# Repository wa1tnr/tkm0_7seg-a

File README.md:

# tkm0_7seg-a
Sat Apr 27 22:03:36 UTC 2019

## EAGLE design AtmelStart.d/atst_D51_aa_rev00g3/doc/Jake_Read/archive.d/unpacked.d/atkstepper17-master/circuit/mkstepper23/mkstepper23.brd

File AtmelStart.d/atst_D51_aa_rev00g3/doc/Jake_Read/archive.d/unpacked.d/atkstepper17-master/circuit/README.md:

# AutomataKit Stepper17 Circuit Design

The circuit uses an ATXmega256A3U microcontroller and a TMC2130 step driver to do the business. Between the two are an SPI bus, to configure the driver, two diagnosis lines, a step, direction, and enable lines.

The TMC2130 is a popular step driver, and can sink ~ 1.5A of current. 

Power is bussed into the board with two M3 Screw Terminals. The board is not polarity protected. Data is delivered on an Automatakit Port, which includes a data line (uart TX / RX) and clock lines (CLKIN and CLKOUT)

## Next Circuit

 - on current scaling, get rid of PWM circuit and line out, use internal ref, and choose resistors with math: want 0.5 - 1.2A to be inside of 16-32 selection
 - go to 2oz copper bc u fancy, etc	
 - get rid of this split gnd

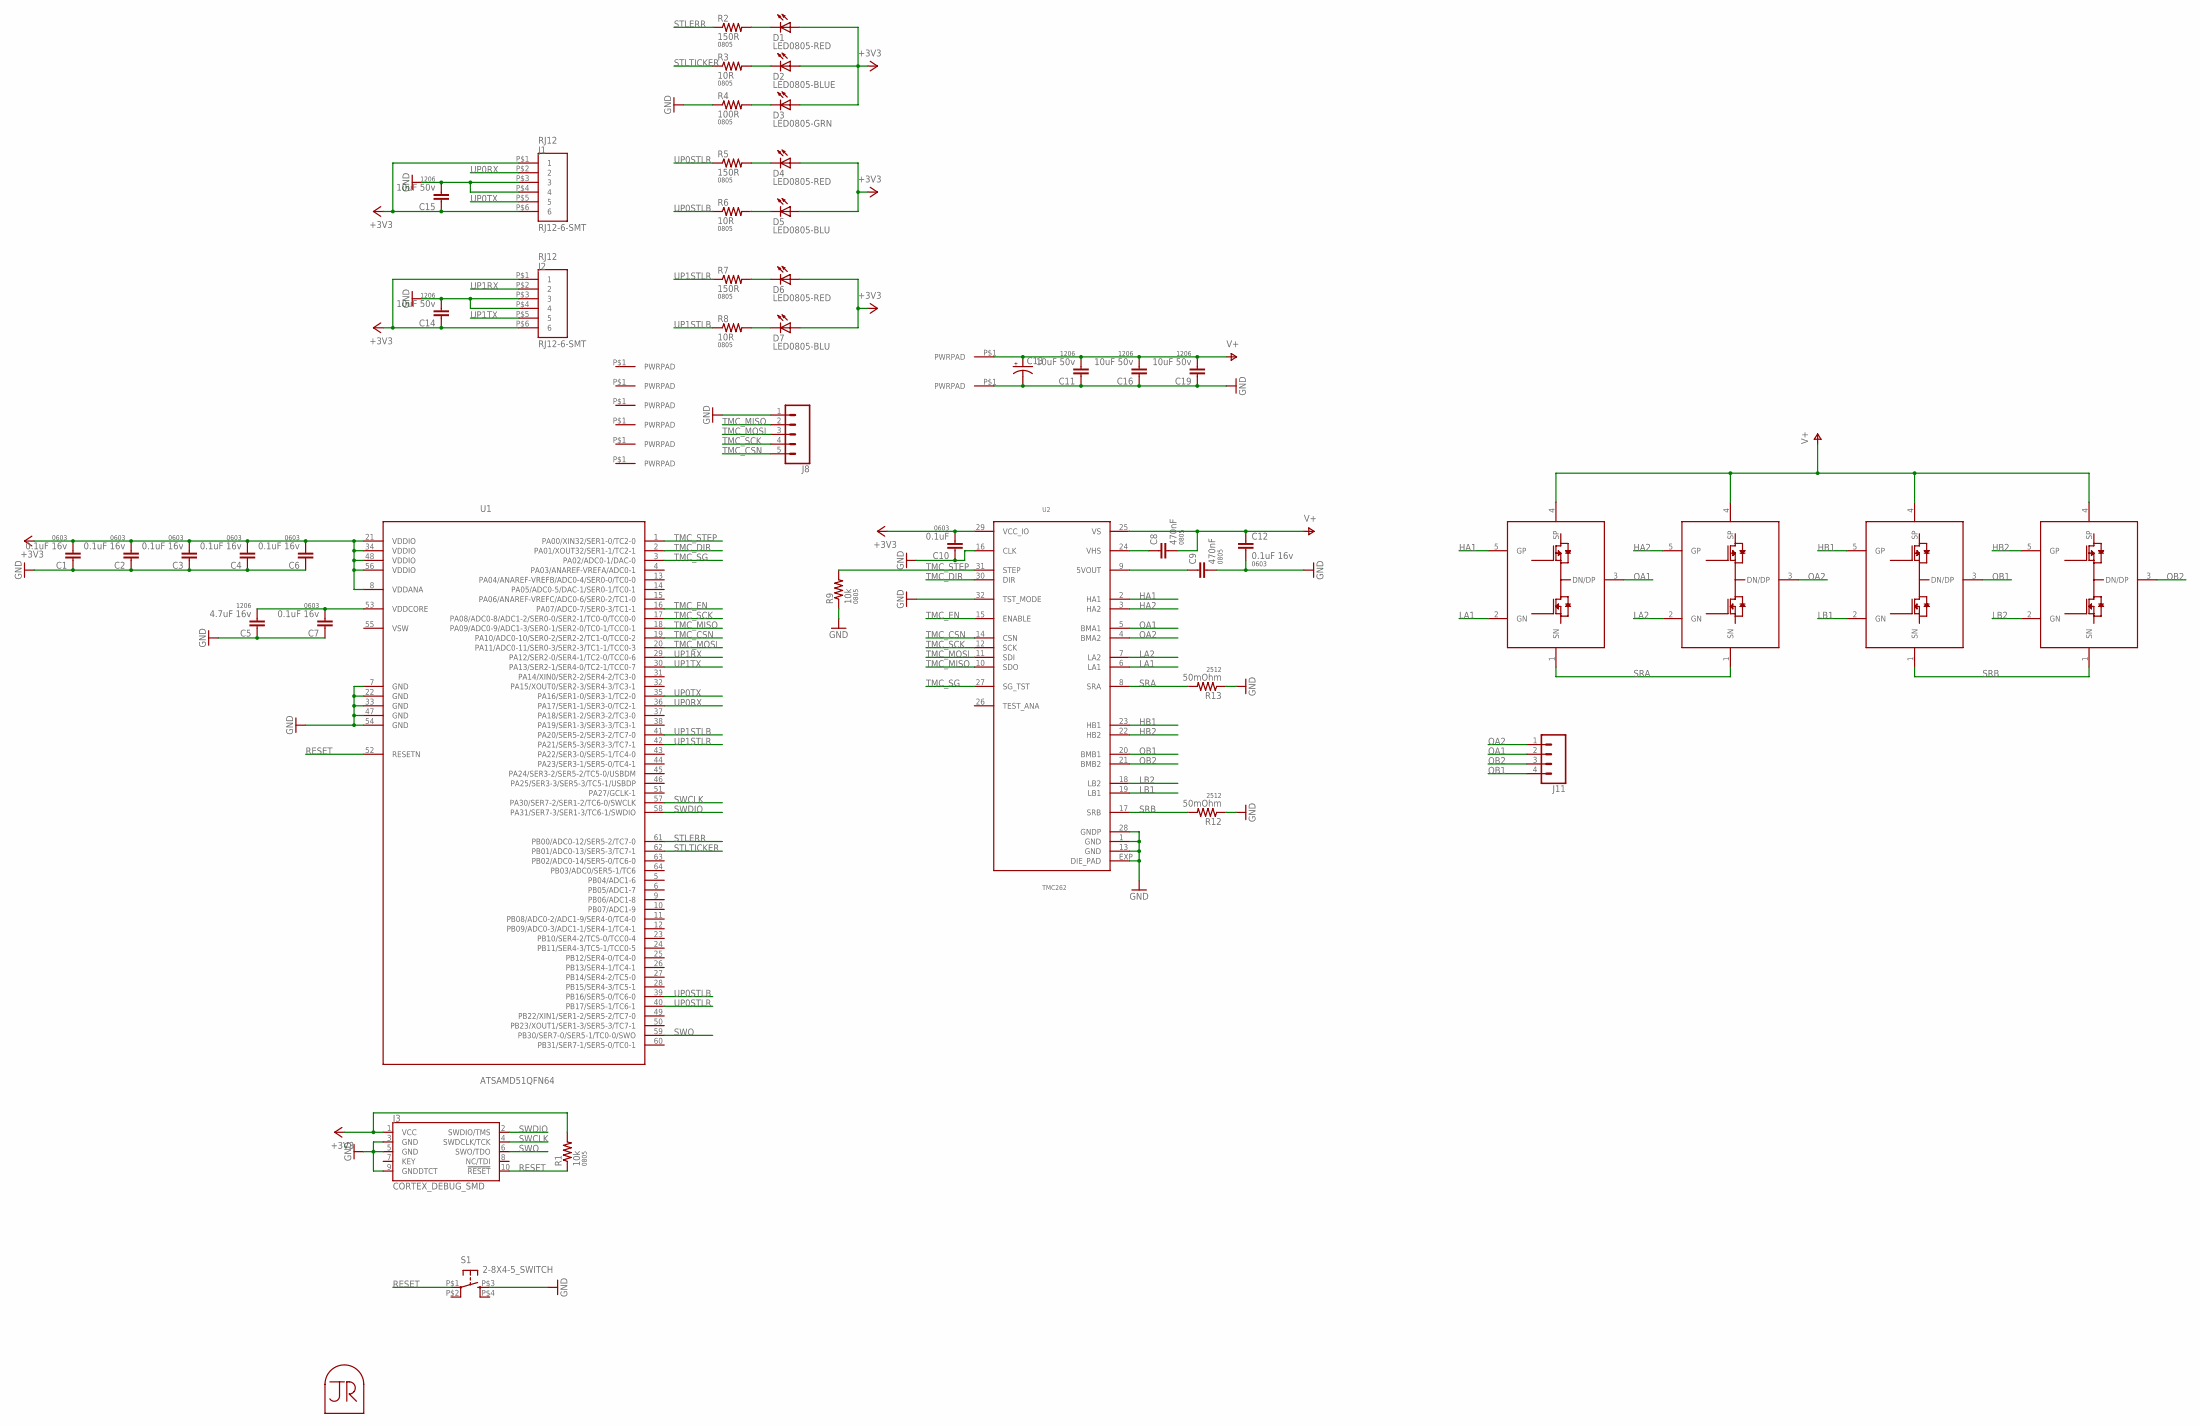
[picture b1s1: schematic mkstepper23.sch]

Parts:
C1, C2, C3, C4, C6, C7, C12: 0.1uF 16v; 0603-CAP
C5: 4.7uF 16v; 1206
C8, C9: 470nF; 0805
C10: 0.1uF; 0603-CAP
C11, C14, C15, C16, C19: 10uF 50v; 1206
C13: CAP-POL-6.6X6.6; 6.6X6.6-CAP
D1, D4, D6: LED0805-RED; LED0805
D2: LED0805-BLUE; LED0805
D3: LED0805-GRN; LED0805
D5, D7: LED0805-BLU; LED0805
J1, J2: RJ12-6-SMT
J3: CORTEX_DEBUG_SMD; SAMTECH_FTSH-105-01
J4, J5, J6, J7, J12, J13: PWRPADM3-SKINNY; PWRPAD_3-25MM-SKINNY
J8: CONN_05NO_SILK; 1X05_NO_SILK
J9, J10: PWRPAD; PWRPAD_M3-PEM-MOUNT
J11: CONN_04LONGPADS; 1X04_LONGPADS
MP1: JRTOMBSTONE
Q1, Q2, Q3, Q4: PNPAIR-FDD8424H; DPAK-5
R1, R9: 10k; 0805
R2, R5, R7: 150R; 0805
R3, R6, R8: 10R; 0805
R4: 100R; 0805
R12, R13: 50mOhm; R2512
S1: 2-8X4-5_SWITCH; TACT-SWITCH-KMR6
U1: ATSAMD51QFN64; QFN-64-9X9MM
U2: TMC262; QFN32

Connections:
+3V3: C1.2, C2.2, C3.2, C4.2, C6.2, C10.2, C14.1, C15.1, D1.1 (A), D2.1 (A), D3.1 (A), D4.1 (A), D5.1 (A), D6.1 (A), D7.1 (A), J1.P$1 (1), J1.P$6 (6), J2.P$1 (1), J2.P$6 (6), J3.1 (VCC), R1.2, U1.8 (VDDANA), U1.21 (VDDIO), U1.34 (VDDIO), U1.48 (VDDIO), U1.56 (VDDIO), U2.29 (VCC_IO)
GND: C1.1, C2.1, C3.1, C4.1, C5.1, C6.1, C7.1, C9.2, C10.1, C11.1, C12.2, C13.-, C14.2, C15.2, C16.1, C19.1, J1.P$3 (3), J1.P$4 (4), J2.P$3 (3), J2.P$4 (4), J3.3 (GND), J3.5 (GND), J3.9 (GNDDTCT), J8.1, J10.P$1, R4.1, R9.1, R12.1, R13.1, S1.P$3 (S), U1.7 (GND), U1.22 (GND), U1.33 (GND), U1.47 (GND), U1.54 (GND), U2.1 (GND), U2.13 (GND), U2.16 (CLK), U2.28 (GNDP), U2.32 (TST_MODE), U2.EXP (DIE_PAD)
HA1: Q1.5 (GP), U2.2 (HA1)
HA2: Q2.5 (GP), U2.3 (HA2)
HB1: Q3.5 (GP), U2.23 (HB1)
HB2: Q4.5 (GP), U2.22 (HB2)
LA1: Q1.2 (GN), U2.6 (LA1)
LA2: Q2.2 (GN), U2.7 (LA2)
LB1: Q3.2 (GN), U2.19 (LB1)
LB2: Q4.2 (GN), U2.18 (LB2)
unnamed: D3.2 (C), R4.2
unnamed: C8.1, U2.24 (VHS)
unnamed: C9.1, U2.9 (5VOUT)
unnamed: D2.2 (C), R3.2
unnamed: D1.2 (C), R2.2
unnamed: C5.2, C7.2, U1.53 (VDDCORE)
unnamed: D4.2 (C), R5.2
unnamed: D5.2 (C), R6.2
unnamed: D6.2 (C), R7.2
unnamed: D7.2 (C), R8.2
OA1: J11.2, Q1.3 (DN/DP), U2.5 (BMA1)
OA2: J11.1, Q2.3 (DN/DP), U2.4 (BMA2)
OB1: J11.4, Q3.3 (DN/DP), U2.20 (BMB1)
OB2: J11.3, Q4.3 (DN/DP), U2.21 (BMB2)
RESET: J3.10 (!RESET), R1.1, S1.P$1, U1.52 (RESETN)
SRA: Q1.1 (SN), Q2.1 (SN), R13.2, U2.8 (SRA)
SRB: Q3.1 (SN), Q4.1 (SN), R12.2, U2.17 (SRB)
STLERR: R2.1, U1.61 (PB00/ADC0-12/SER5-2/TC7-0)
STLTICKER: R3.1, U1.62 (PB01/ADC0-13/SER5-3/TC7-1)
SWCLK: J3.4 (SWDCLK/TCK), U1.57 (PA30/SER7-2/SER1-2/TC6-0/SWCLK)
SWDIO: J3.2 (SWDIO/TMS), U1.58 (PA31/SER7-3/SER1-3/TC6-1/SWDIO)
SWO: J3.6 (SWO/TDO), U1.59 (PB30/SER7-0/SER5-1/TC0-0/SWO)
TMC_CSN: J8.5, U1.19 (PA10/ADC0-10/SER0-2/SER2-2/TC1-0/TCC0-2), U2.14 (CSN)
TMC_DIR: U1.2 (PA01/XOUT32/SER1-1/TC2-1), U2.30 (DIR)
TMC_EN: U1.16 (PA07/ADC0-7/SER0-3/TC1-1), U2.15 (ENABLE)
TMC_MISO: J8.2, U1.18 (PA09/ADC0-9/ADC1-3/SER0-1/SER2-0/TC0-1/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), U2.10 (SDO)
TMC_MOSI: J8.3, U1.20 (PA11/ADC0-11/SER0-3/SER2-3/TC1-1/TCC0-3), U2.11 (SDI)
TMC_SCK: J8.4, U1.17 (PA08/ADC0-8/ADC1-2/SER0-0/SER2-1/TC0-0/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), U2.12 (SCK)
TMC_SG: U1.3 (PA02/ADC0-1/DAC-0), U2.27 (SG_TST)
TMC_STEP: R9.2, U1.1 (PA00/XIN32/SER1-0/TC2-0), U2.31 (STEP)
UP0RX: J1.P$2 (2), U1.36 (PA17/SER1-1/SER3-0/TC2-1)
UP0STLB: R6.1, U1.39 (PB16/SER5-0/TC6-0)
UP0STLR: R5.1, U1.40 (PB17/SER5-1/TC6-1)
UP0TX: J1.P$5 (5), U1.35 (PA16/SER1-0/SER3-1/TC2-0)
UP1RX: J2.P$2 (2), U1.29 (PA12/SER2-0/SER4-1/TC2-0/TCC0-6)
UP1STLB: R8.1, U1.41 (PA20/SER5-2/SER3-2/TC7-0)
UP1STLR: R7.1, U1.42 (PA21/SER5-3/SER3-3/TC7-1)
UP1TX: J2.P$5 (5), U1.30 (PA13/SER2-1/SER4-0/TC2-1/TCC0-7)
V+: C8.2, C11.2, C12.1, C13.+, C16.2, C19.2, J9.P$1, Q1.4 (SP), Q2.4 (SP), Q3.4 (SP), Q4.4 (SP), U2.25 (VS)

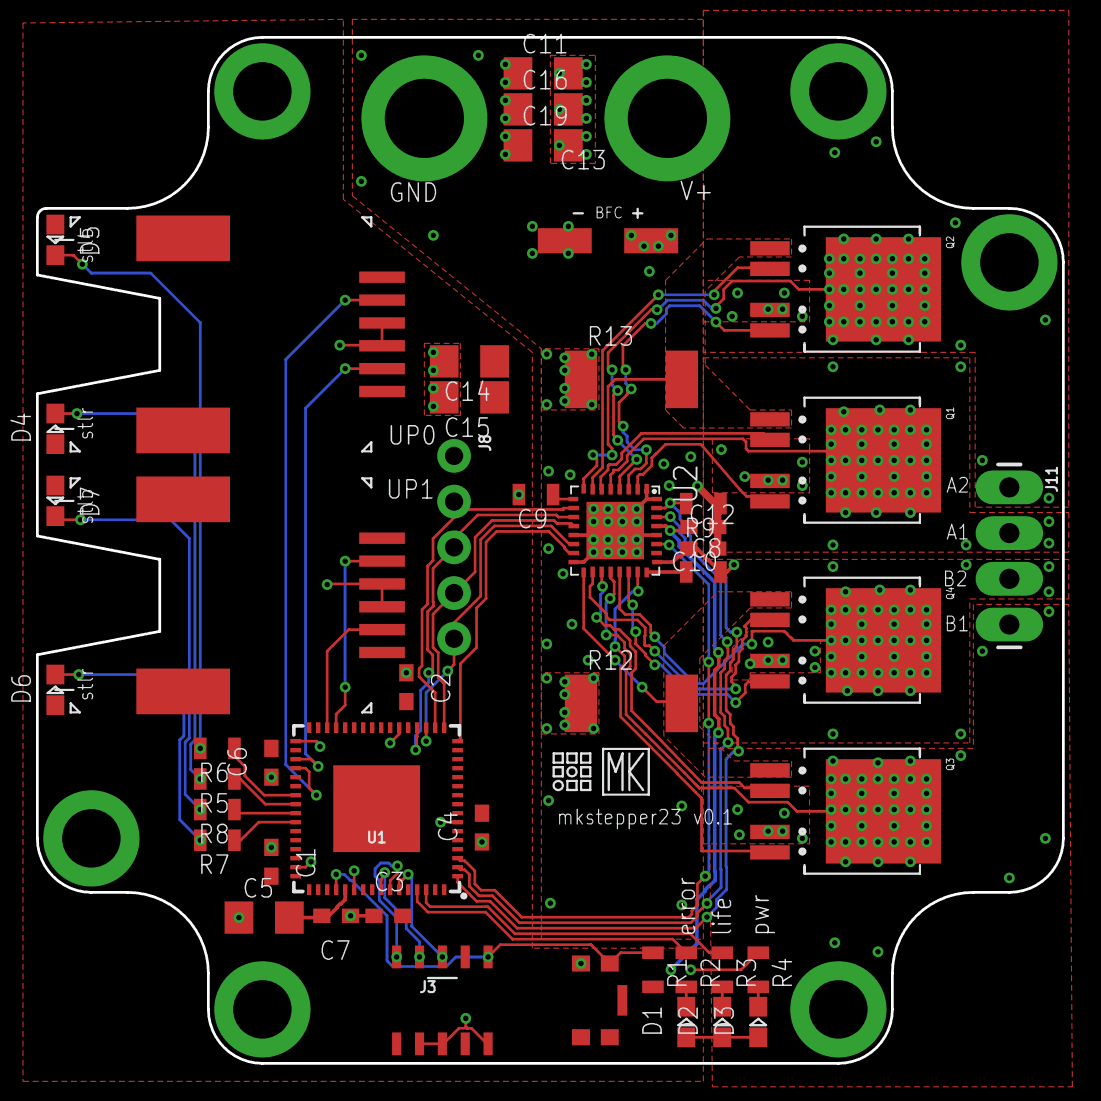
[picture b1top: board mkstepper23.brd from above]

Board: 2 copper layers, 57.0 x 57.0 mm, 58 parts (1 on the bottom side), 49 nets.

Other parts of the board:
U$5: CBA-SILK-LOGO
U$9: MK-LOGO-SILK

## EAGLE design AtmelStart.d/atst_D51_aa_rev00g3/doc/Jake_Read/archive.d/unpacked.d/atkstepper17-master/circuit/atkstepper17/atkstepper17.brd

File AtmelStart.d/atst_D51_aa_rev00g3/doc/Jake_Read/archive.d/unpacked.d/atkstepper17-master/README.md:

# AutomataKit Stepper17

This is a motor driver for Nema 17 size Stepper Motors, which extends the [automatakit](https://gitlab.cba.mit.edu/jakeread/automatakit) architecture.

The board receives commands from an automatakit network and faithfully executes them, replying when complete. 

## Development Notes

See [circuit chatter](/circuit) and [firmware chatter](/embedded).

# Viable Commands

### Test

Keycode: **127**
 - to test networking, this will reply with a payload packet containing ```127, 12, 24, 48``` and will toggle an LED on the board

### Reset

Keycode: **128**
 - issues a software microcontroller reset
 - if the microcontroller is already hung up, this will not work

### Step Trapezoid

Keycode: **131**
Arguments: Steps to Make, int32_t | Entry Speed, steps/s, uint32_t | Acceleration Rate, steps/s/s, uint32_t | Acceleration Length, steps to accelerate for, uint32_t | Decceleration Length, steps to deccelerate after, uint32_t
Returns: Steps Made, int32_t | on step completion
 - the stepper will load this block into its stepping buffer, and if the buffer is empty will execute the trapezoid. on it's completion, the stepper will reply with an acknowledgement

### Step Wait

Keycode: **133**
Arguments: Steps to Make, int32_t | Entry Speed, steps/s, uint32_t | Acceleration Rate, steps/s/s, uint32_t | Acceleration Length, steps to accelerate for, uint32_t | Decceleration Length, steps to deccelerate after, uint32_t
Returns: Wait Made, uint8_t *24*
 - an identical block to the step trapezoid, but with a flag to avoid actually stepping. this is used in motion planning to insert a wait block for a motor with zero steps, to retain packet synchronization

# Reproducing This Work

All automatakit works are open source, and while we cannot sell you boards, if you have an interesting application, get in touch to ask about collaborating.

To reproduce boards and load code, see the document ['Reproducing Automatakit Work'](https://gitlab.cba.mit.edu/jakeread/automatakit/reproducing)

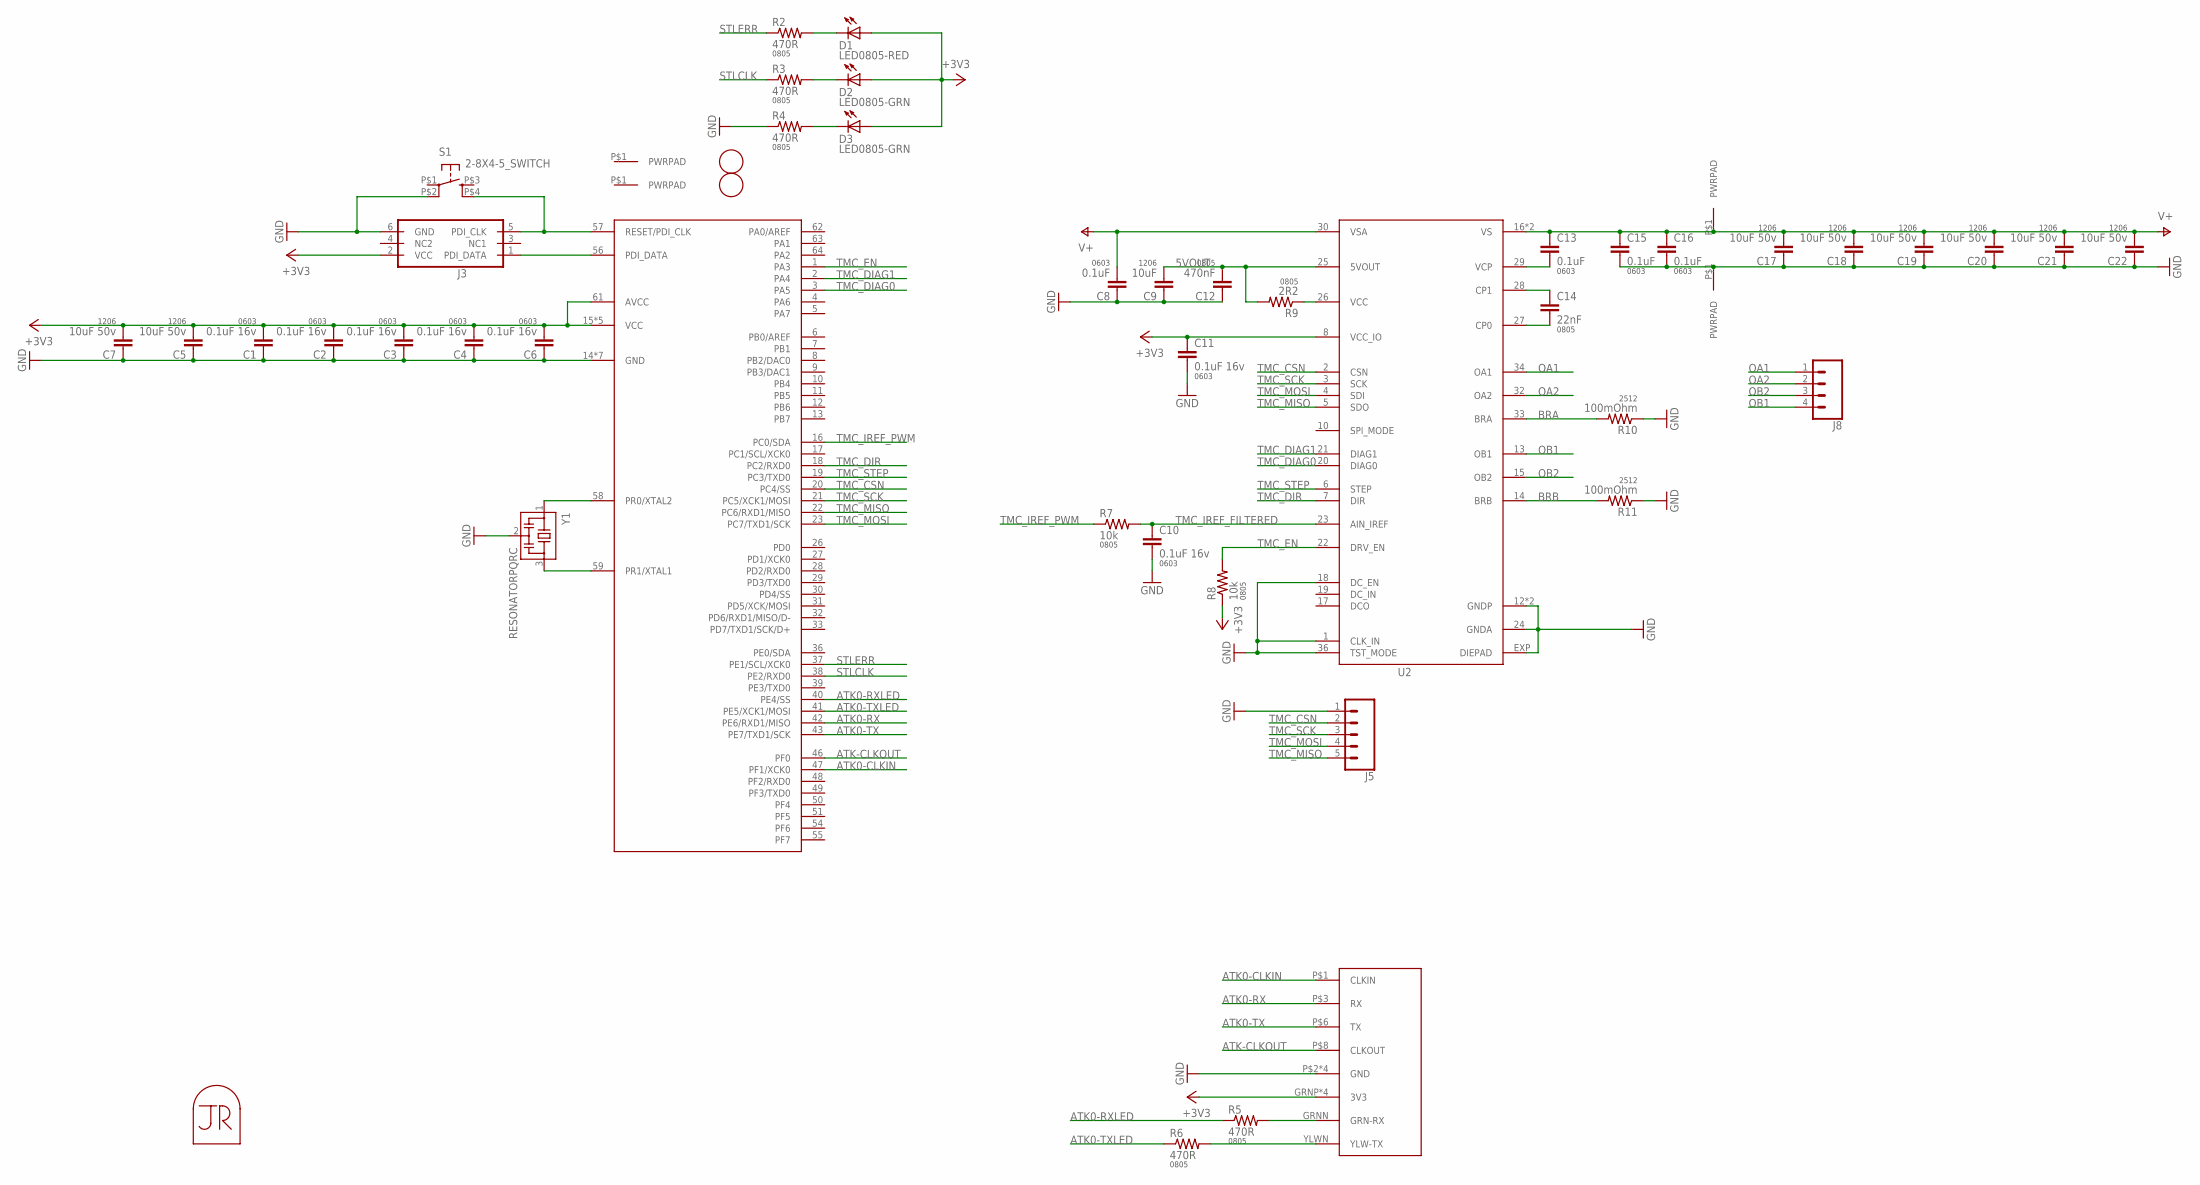
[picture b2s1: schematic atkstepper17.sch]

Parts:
C1, C2, C3, C4, C6, C10, C11: 0.1uF 16v; 0603-CAP
C5, C7, C17, C18, C19, C20, C21, C22: 10uF 50v; 1206
C8, C13, C15, C16: 0.1uF; 0603-CAP
C9: 10uF; 1206
C12: 470nF; 0805
C14: 22nF; 0805
D1: LED0805-RED; LED0805
D2, D3: LED0805-GRN; LED0805
J1, J2: PWRPADM3; PWRPAD_3-25MM
J3: PDIFEMALE_SMD; PDI_2X3_SMD
J4: ATK-PHY; RJ45-LED-RJE7318800XXX
J5: CONN_05NO_SILK; 1X05_NO_SILK
J6, J7: PWRPAD; PWRPAD_M3-PEM-MOUNT
J8: CONN_04LONGPADS; 1X04_LONGPADS
MP1: JRTOMBSTONE
R2, R3, R4, R5, R6: 470R; 0805
R7, R8: 10k; 0805
R9: 2R2; 0805
R10, R11: 100mOhm; R2512
S1: 2-8X4-5_SWITCH; TACT-SWITCH-KMR6
U1: ATXMEGA_A3UQFN; QFN-64-9X9MM
U2: TMC2130; QFN36-5X6
U$1, U$2: FIDUCIAL; FIDUCIAL_1MM
Y1: RESONATORPQRC; RES_PRQC

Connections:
5VOUT: C9.2, C12.2, R9.2, U2.25 (5VOUT)
+3V3: C1.2, C2.2, C3.2, C4.2, C5.2, C6.2, C7.2, C11.1, D1.1 (A), D2.1 (A), D3.1 (A), J3.2 (VCC), J4.GRNP (3V3), J4.P$4 (3V3), J4.P$5 (3V3), J4.YLWP (3V3), R8.1, U1.15 (VCC), U1.25 (VCC), U1.35 (VCC), U1.45 (VCC), U1.53 (VCC), U1.61 (AVCC), U2.8 (VCC_IO)
ATK0-CLKIN: J4.P$1 (CLKIN), U1.47 (PF1/XCK0)
ATK0-RX: J4.P$3 (RX), U1.42 (PE6/RXD1/MISO)
ATK0-RXLED: R5.1, U1.40 (PE4/SS)
ATK0-TX: J4.P$6 (TX), U1.43 (PE7/TXD1/SCK)
ATK0-TXLED: R6.1, U1.41 (PE5/XCK1/MOSI)
ATK-CLKOUT: J4.P$8 (CLKOUT), U1.46 (PF0)
BRA: R10.2, U2.33 (BRA)
BRB: R11.2, U2.14 (BRB)
GND: C1.1, C2.1, C3.1, C4.1, C5.1, C6.1, C7.1, C8.1, C9.1, C10.2, C11.2, C12.1, C15.2, C16.2, C17.1, C18.1, C19.1, C20.1, C21.1, C22.1, J3.6 (GND), J4.P$2 (GND), J4.P$7 (GND), J4.SHDL1 (GND), J4.SHDL2 (GND), J5.1, J7.P$1, R4.1, R10.1, R11.1, S1.P$2 (P1), U1.14 (GND), U1.24 (GND), U1.34 (GND), U1.44 (GND), U1.52 (GND), U1.60 (GND), U1.P$1 (GND), U2.1 (CLK_IN), U2.12 (GNDP), U2.18 (DC_EN), U2.24 (GNDA), U2.35 (GNDP), U2.36 (TST_MODE), U2.EXP (DIEPAD), Y1.2
unnamed: D3.2 (C), R4.2
unnamed: J3.5 (PDI_CLK), S1.P$4 (S1), U1.57 (RESET/PDI_CLK)
unnamed: U1.58 (PR0/XTAL2), Y1.1
unnamed: U1.59 (PR1/XTAL1), Y1.3
unnamed: D2.2 (C), R3.2
unnamed: D1.2 (C), R2.2
unnamed: J3.1 (PDI_DATA), U1.56 (PDI_DATA)
unnamed: C14.2, U2.27 (CP0)
unnamed: R9.1, U2.26 (VCC)
unnamed: C14.1, U2.28 (CP1)
unnamed: C13.2, U2.29 (VCP)
unnamed: J4.GRNN (GRN-RX), R5.2
unnamed: J4.YLWN (YLW-TX), R6.2
OA1: J8.1, U2.34 (OA1)
OA2: J8.2, U2.32 (OA2)
OB1: J8.4, U2.13 (OB1)
OB2: J8.3, U2.15 (OB2)
STLCLK: R3.1, U1.38 (PE2/RXD0)
STLERR: R2.1, U1.37 (PE1/SCL/XCK0)
TMC_CSN: J5.2, U1.20 (PC4/SS), U2.2 (CSN)
TMC_DIAG0: U1.3 (PA5), U2.20 (DIAG0)
TMC_DIAG1: U1.2 (PA4), U2.21 (DIAG1)
TMC_DIR: U1.18 (PC2/RXD0), U2.7 (DIR)
TMC_EN: R8.2, U1.1 (PA3), U2.22 (DRV_EN)
TMC_IREF_FILTERED: C10.1, R7.2, U2.23 (AIN_IREF)
TMC_IREF_PWM: R7.1, U1.16 (PC0/SDA)
TMC_MISO: J5.5, U1.22 (PC6/RXD1/MISO), U2.5 (SDO)
TMC_MOSI: J5.4, U1.23 (PC7/TXD1/SCK), U2.4 (SDI)
TMC_SCK: J5.3, U1.21 (PC5/XCK1/MOSI), U2.3 (SCK)
TMC_STEP: U1.19 (PC3/TXD0), U2.6 (STEP)
V+: C8.2, C13.1, C15.1, C16.1, C17.2, C18.2, C19.2, C20.2, C21.2, C22.2, J6.P$1, U2.16 (VS), U2.30 (VSA), U2.31 (VS)

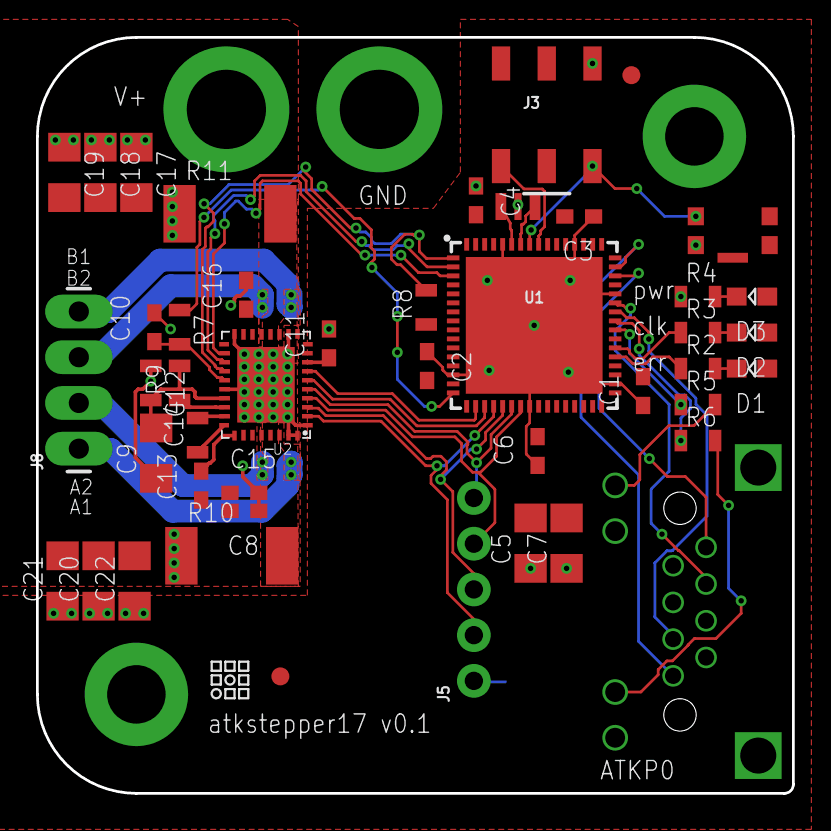
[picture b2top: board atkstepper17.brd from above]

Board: 2 copper layers, 42.0 x 42.0 mm, 51 parts (1 on the bottom side), 42 nets.

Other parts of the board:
U$5: CBA-SILK-LOGO

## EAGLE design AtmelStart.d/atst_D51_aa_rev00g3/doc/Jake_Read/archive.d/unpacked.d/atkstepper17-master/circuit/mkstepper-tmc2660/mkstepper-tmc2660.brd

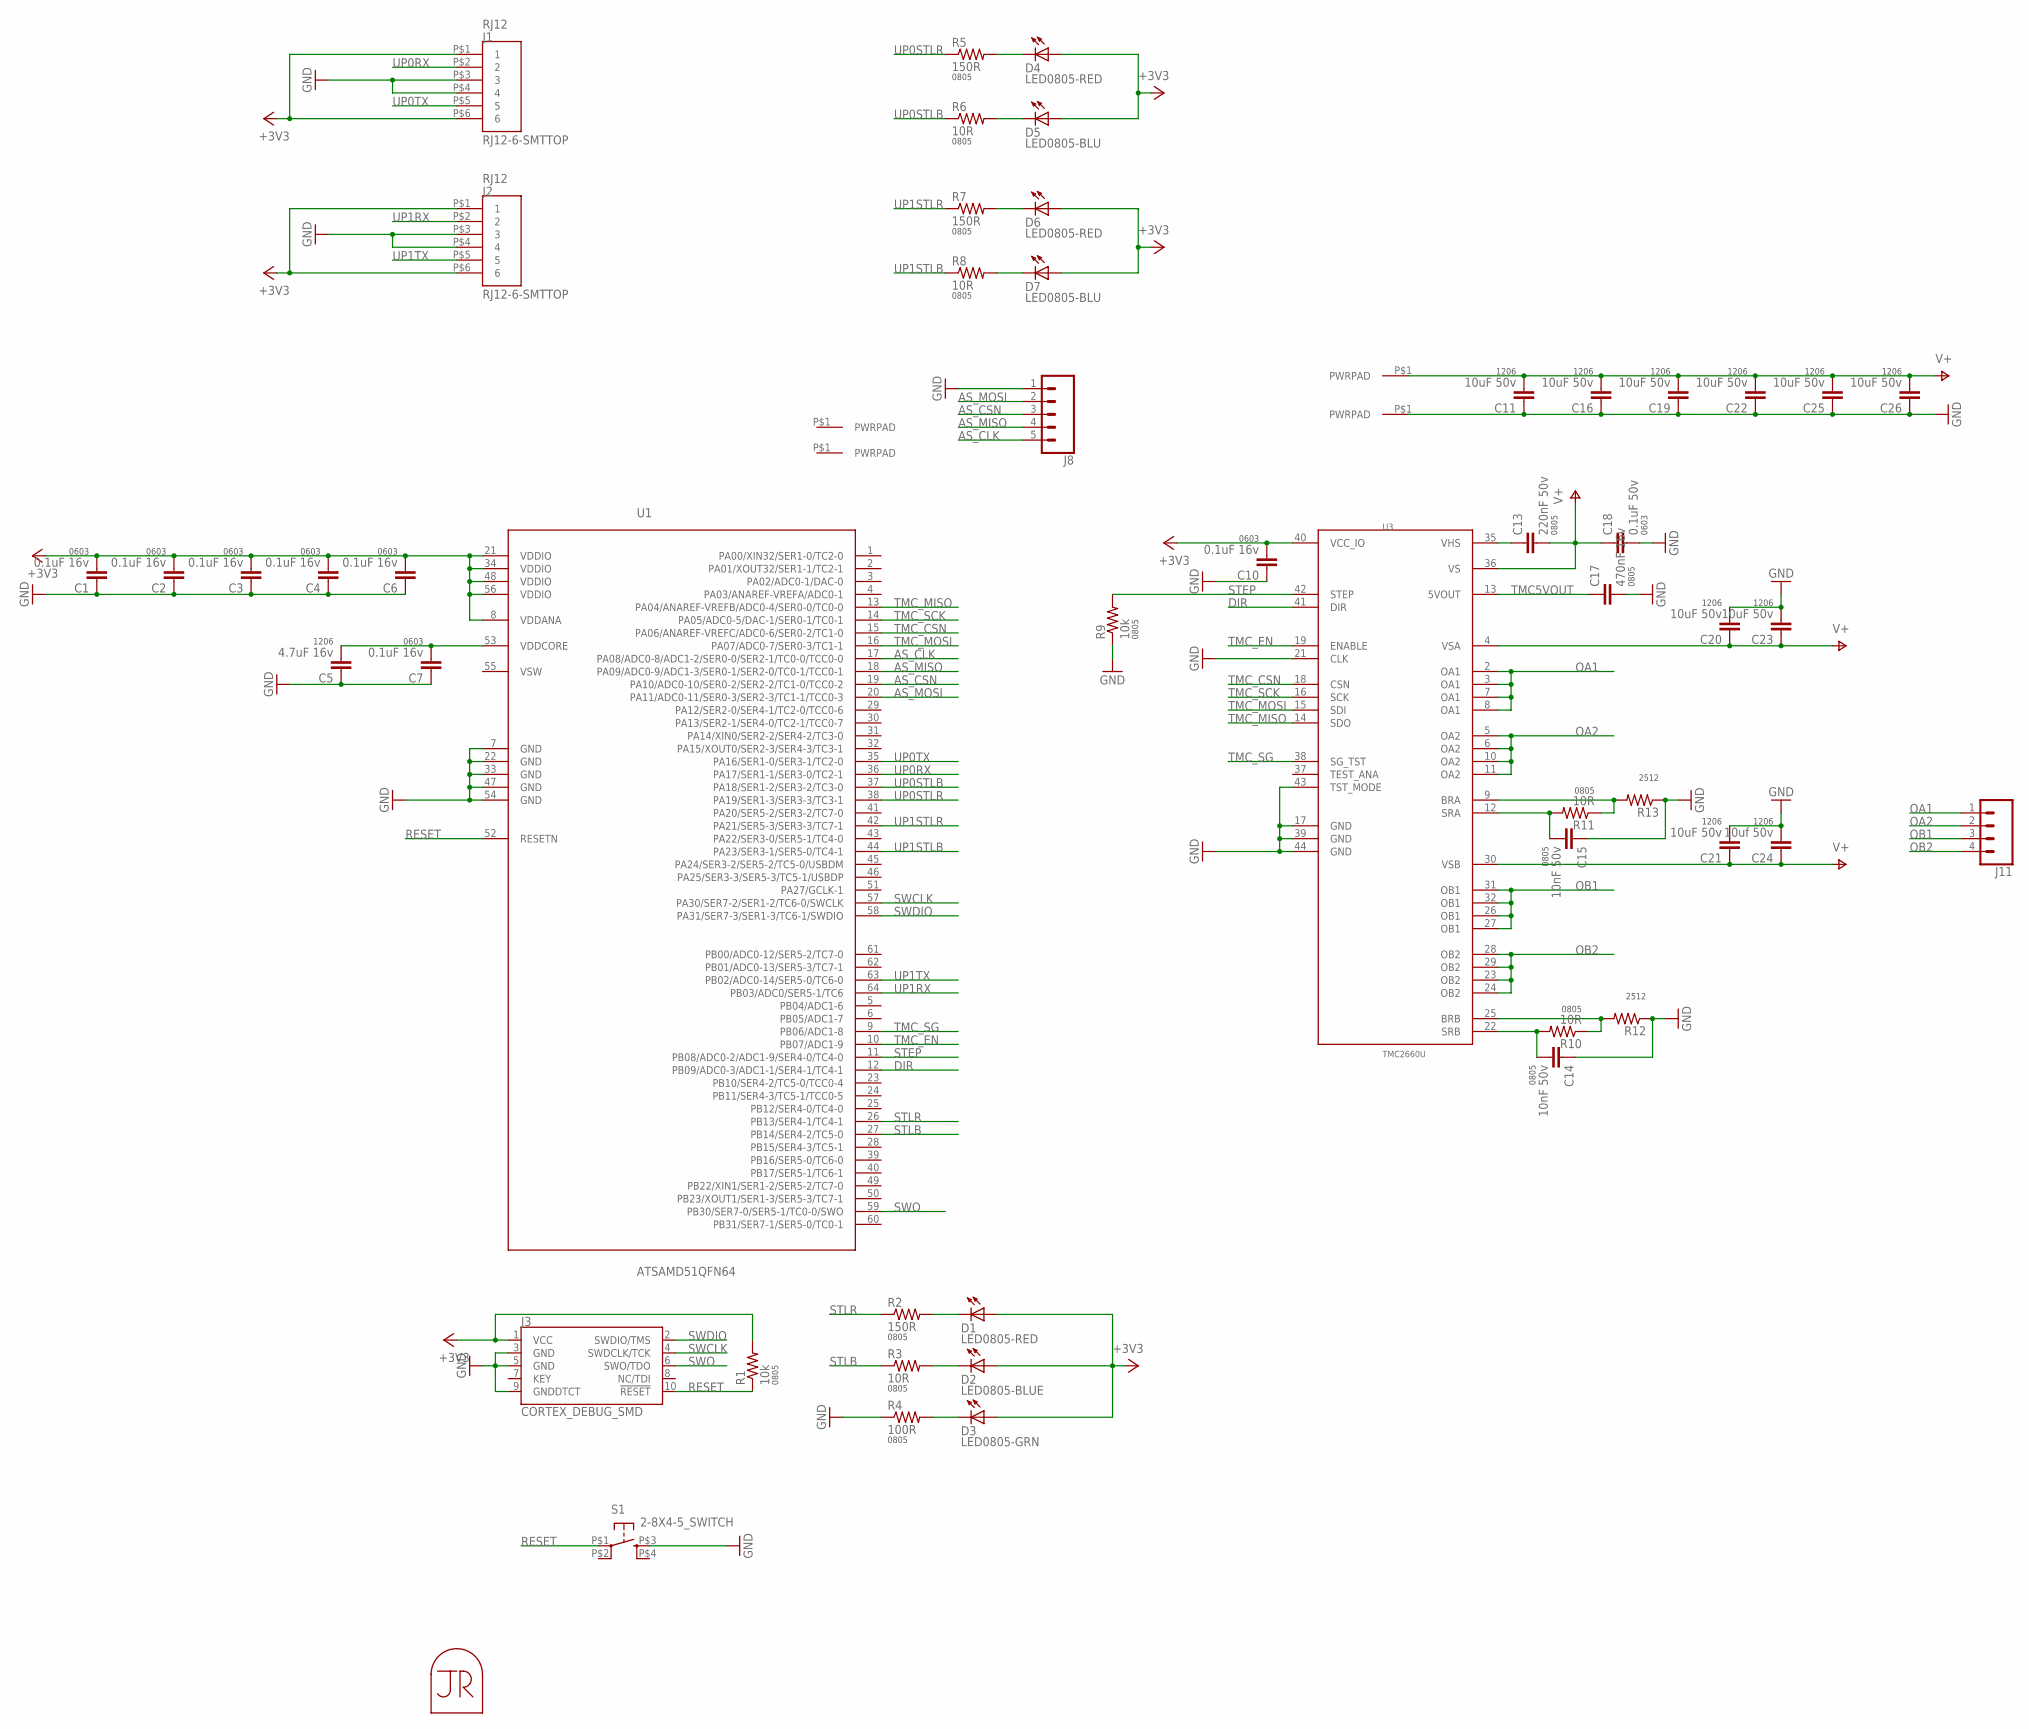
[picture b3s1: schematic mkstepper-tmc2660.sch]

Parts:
C1, C2, C3, C4, C6, C7, C10: 0.1uF 16v; 0603-CAP
C5: 4.7uF 16v; 1206
C11, C16, C19, C20, C21, C22, C23, C25, C26: 10uF 50v; 1206
C13: 220nF 50v; 0805
C14, C15: 10nF 50v; 0805
C17: 470nF 16v; 0805
C18: 0.1uF 50v; 0603-CAP
C24: 10uf 50v; 1206
D1, D4, D6: LED0805-RED; LED0805
D2: LED0805-BLUE; LED0805
D3: LED0805-GRN; LED0805
D5, D7: LED0805-BLU; LED0805
J1, J2: RJ12-6-SMTTOP; RJ12-6-SMT-TOPENTRY
J3: CORTEX_DEBUG_SMD; SAMTECH_FTSH-105-01
J6, J7: PWRPADM3; PWRPAD_3-25MM
J8: CONN_05NO_SILK; 1X05_NO_SILK
J9, J10: PWRPAD; PWRPAD_M3-PEM-MOUNT
J11: CONN_04LONGPADS; 1X04_LONGPADS
MP1: JRTOMBSTONE
R1, R9: 10k; 0805
R2, R5, R7: 150R; 0805
R3, R6, R8, R10, R11: 10R; 0805
R4: 100R; 0805
R12, R13: RESISTOR2512; R2512
S1: 2-8X4-5_SWITCH; TACT-SWITCH-KMR6
U1: ATSAMD51QFN64; QFN-64-9X9MM
U3: TMC2660U; TQFP44

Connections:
+3V3: C1.2, C2.2, C3.2, C4.2, C6.2, C10.2, D1.1 (A), D2.1 (A), D3.1 (A), D4.1 (A), D5.1 (A), D6.1 (A), D7.1 (A), J1.P$1 (1), J1.P$6 (6), J2.P$1 (1), J2.P$6 (6), J3.1 (VCC), R1.2, U1.8 (VDDANA), U1.21 (VDDIO), U1.34 (VDDIO), U1.48 (VDDIO), U1.56 (VDDIO), U3.40 (VCC_IO)
AS_CLK: J8.5, U1.17 (PA08/ADC0-8/ADC1-2/SER0-0/SER2-1/TC0-0/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)
AS_CSN: J8.3, U1.19 (PA10/ADC0-10/SER0-2/SER2-2/TC1-0/TCC0-2)
AS_MISO: J8.4, U1.18 (PA09/ADC0-9/ADC1-3/SER0-1/SER2-0/TC0-1/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)
AS_MOSI: J8.2, U1.20 (PA11/ADC0-11/SER0-3/SER2-3/TC1-1/TCC0-3)
BRA: R11.1, R13.2, U3.9 (BRA)
BRB: R10.1, R12.2, U3.25 (BRB)
DIR: U1.12 (PB09/ADC0-3/ADC1-1/SER4-1/TC4-1), U3.41 (DIR)
GND: C1.1, C2.1, C3.1, C4.1, C5.1, C6.1, C7.1, C10.1, C11.1, C14.1, C15.1, C16.1, C17.2, C18.2, C19.1, C20.2, C21.2, C22.1, C23.2, C24.2, C25.1, C26.1, J1.P$3 (3), J1.P$4 (4), J2.P$3 (3), J2.P$4 (4), J3.3 (GND), J3.5 (GND), J3.9 (GNDDTCT), J8.1, J10.P$1, R4.1, R9.1, R12.1, R13.1, S1.P$3 (S), U1.7 (GND), U1.22 (GND), U1.33 (GND), U1.47 (GND), U1.54 (GND), U3.17 (GND), U3.21 (CLK), U3.39 (GND), U3.43 (TST_MODE), U3.44 (GND)
unnamed: D3.2 (C), R4.2
unnamed: C13.1, U3.35 (VHS)
unnamed: D2.2 (C), R3.2
unnamed: D1.2 (C), R2.2
unnamed: C5.2, C7.2, U1.53 (VDDCORE)
unnamed: D4.2 (C), R5.2
unnamed: D5.2 (C), R6.2
unnamed: D6.2 (C), R7.2
unnamed: D7.2 (C), R8.2
OA1: J11.1, U3.2 (OA1), U3.3 (OA1), U3.7 (OA1), U3.8 (OA1)
OA2: J11.2, U3.5 (OA2), U3.6 (OA2), U3.10 (OA2), U3.11 (OA2)
OB1: J11.3, U3.26 (OB1), U3.27 (OB1), U3.31 (OB1), U3.32 (OB1)
OB2: J11.4, U3.23 (OB2), U3.24 (OB2), U3.28 (OB2), U3.29 (OB2)
RESET: J3.10 (!RESET), R1.1, S1.P$1, U1.52 (RESETN)
SRA: C15.2, R11.2, U3.12 (SRA)
SRB: C14.2, R10.2, U3.22 (SRB)
STEP: R9.2, U1.11 (PB08/ADC0-2/ADC1-9/SER4-0/TC4-0), U3.42 (STEP)
STLB: R3.1, U1.27 (PB14/SER4-2/TC5-0)
STLR: R2.1, U1.26 (PB13/SER4-1/TC4-1)
SWCLK: J3.4 (SWDCLK/TCK), U1.57 (PA30/SER7-2/SER1-2/TC6-0/SWCLK)
SWDIO: J3.2 (SWDIO/TMS), U1.58 (PA31/SER7-3/SER1-3/TC6-1/SWDIO)
SWO: J3.6 (SWO/TDO), U1.59 (PB30/SER7-0/SER5-1/TC0-0/SWO)
TMC5VOUT: C17.1, U3.13 (5VOUT)
TMC_CSN: U1.15 (PA06/ANAREF-VREFC/ADC0-6/SER0-2/TC1-0), U3.18 (CSN)
TMC_EN: U1.10 (PB07/ADC1-9), U3.19 (ENABLE)
TMC_MISO: U1.13 (PA04/ANAREF-VREFB/ADC0-4/SER0-0/TC0-0), U3.14 (SDO)
TMC_MOSI: U1.16 (PA07/ADC0-7/SER0-3/TC1-1), U3.15 (SDI)
TMC_SCK: U1.14 (PA05/ADC0-5/DAC-1/SER0-1/TC0-1), U3.16 (SCK)
TMC_SG: U1.9 (PB06/ADC1-8), U3.38 (SG_TST)
UP0RX: J1.P$2 (2), U1.36 (PA17/SER1-1/SER3-0/TC2-1)
UP0STLB: R6.1, U1.37 (PA18/SER1-2/SER3-2/TC3-0)
UP0STLR: R5.1, U1.38 (PA19/SER1-3/SER3-3/TC3-1)
UP0TX: J1.P$5 (5), U1.35 (PA16/SER1-0/SER3-1/TC2-0)
UP1RX: J2.P$2 (2), U1.64 (PB03/ADC0/SER5-1/TC6)
UP1STLB: R8.1, U1.44 (PA23/SER3-1/SER5-0/TC4-1)
UP1STLR: R7.1, U1.42 (PA21/SER5-3/SER3-3/TC7-1)
UP1TX: J2.P$5 (5), U1.63 (PB02/ADC0-14/SER5-0/TC6-0)
V+: C11.2, C13.2, C16.2, C18.1, C19.2, C20.1, C21.1, C22.2, C23.1, C24.1, C25.2, C26.2, J9.P$1, U3.4 (VSA), U3.30 (VSB), U3.36 (VS)

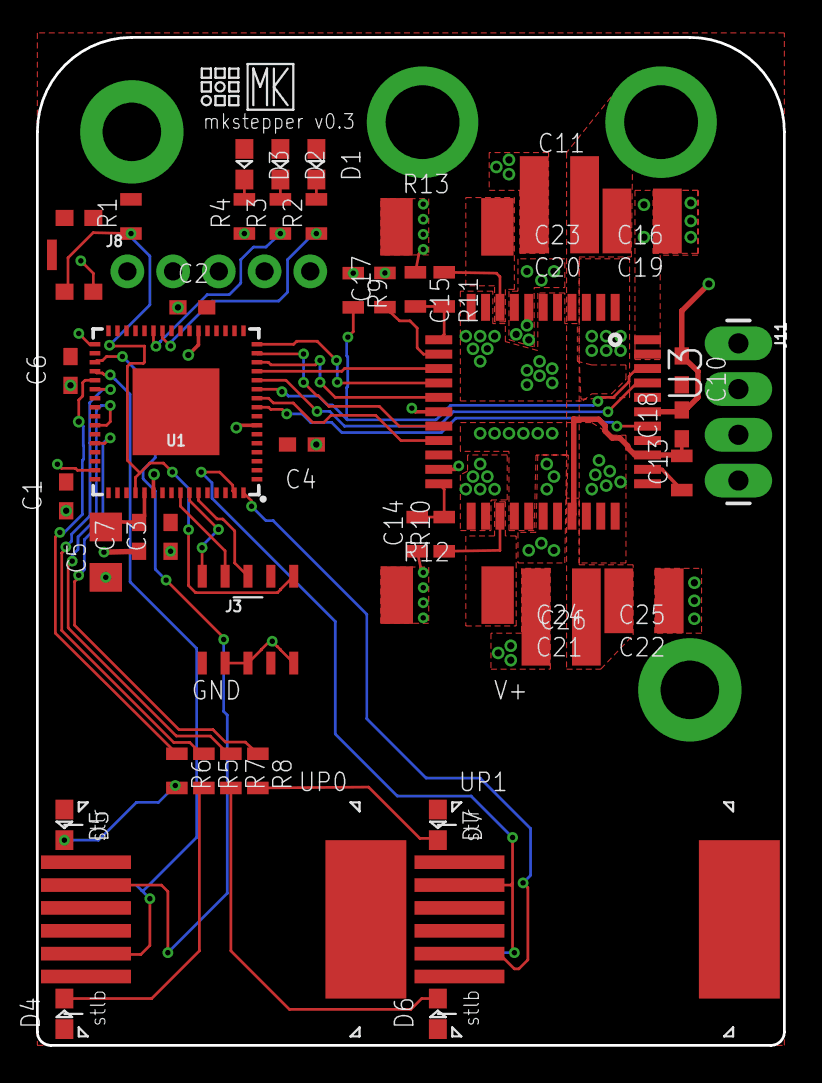
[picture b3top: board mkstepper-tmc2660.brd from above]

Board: 2 copper layers, 41.5 x 56.0 mm, 58 parts (1 on the bottom side), 47 nets.

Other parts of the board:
U$5: CBA-SILK-LOGO
U$9: MK-LOGO-SILK

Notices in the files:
parts and their libraries:
SparkFun-Connectors: Licensing: Creative Commons ShareAlike 4.0 International - https://creativecommons.org/licenses/by-sa/4.0
